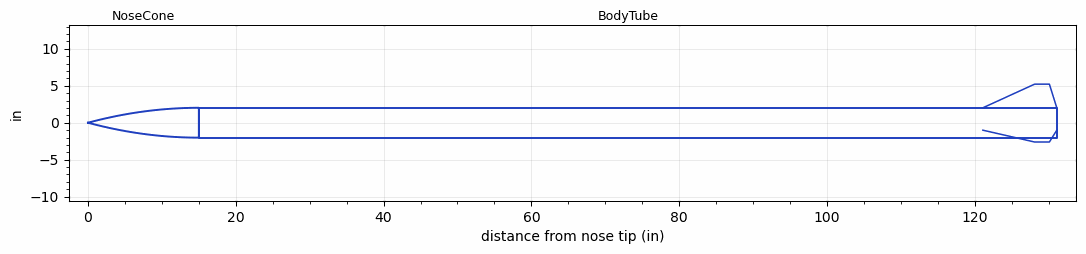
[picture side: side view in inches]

<RASAeroDocument>
 <FileVersion>2</FileVersion>
 <RocketDesign>
  <NoseCone>
   <Length>15</Length>
   <Diameter>4.04</Diameter>
   <Shape>Parabolic</Shape>
   <BluntRadius>0.0625</BluntRadius>
   <Location>0</Location>
  </NoseCone>
  <BodyTube>
   <Length>116.1</Length>
   <Diameter>4.04</Diameter>
   <LaunchShoeArea>0.09</LaunchShoeArea>
   <Location>15</Location>
   <Fin>
    <Count>3</Count>
    <Chord>10</Chord>
    <Span>3.2</Span>
    <SweepDistance>7</SweepDistance>
    <TipChord>2</TipChord>
    <Thickness>0.25</Thickness>
    <LERadius>0.125</LERadius>
    <Location>10</Location>
    <AirfoilSection>Double Wedge</AirfoilSection>
    <FX1>1</FX1>
   </Fin>
  </BodyTube>
  <Surface>Rough Camouflage Paint</Surface>
  <ModifiedBarrowman>True</ModifiedBarrowman>
  <Turbulence>False</Turbulence>
  <UseBooster1>False</UseBooster1>
  <UseBooster2>False</UseBooster2>
 </RocketDesign>
 <LaunchSite>
  <Altitude>4596</Altitude>
  <Pressure>0</Pressure>
  <RodAngle>5</RodAngle>
  <RodLength>18</RodLength>
  <Temperature>100</Temperature>
  <WindSpeed>5</WindSpeed>
 </LaunchSite>
 <Recovery>
  <Altitude1>1000</Altitude1>
  <Altitude2>1500</Altitude2>
  <DeviceType1>Parachute</DeviceType1>
  <DeviceType2>Parachute</DeviceType2>
  <Event1>True</Event1>
  <Event2>True</Event2>
  <Size1>30.57</Size1>
  <Size2>157.2</Size2>
  <EventType1>Apogee</EventType1>
  <EventType2>Altitude</EventType2>
  <CD1>0.75</CD1>
  <CD2>0.928</CD2>
 </Recovery>
 <SimulationList>
  <Simulation>
   <SustainerEngine>N2900-CL  (CTI)</SustainerEngine>
   <SustainerLaunchWt>72.49</SustainerLaunchWt>
   <SustainerNozzleDiameter>2</SustainerNozzleDiameter>
   <SustainerCG>75.91</SustainerCG>
   <SustainerIgnitionDelay>0</SustainerIgnitionDelay>
   <Booster1SeparationDelay>0</Booster1SeparationDelay>
   <Booster1IgnitionDelay>0</Booster1IgnitionDelay>
   <IncludeBooster1>False</IncludeBooster1>
   <Booster2Delay>0</Booster2Delay>
   <IncludeBooster2>False</IncludeBooster2>
   <TimetoApogee>42.08894</TimetoApogee>
   <MaxAltitude>30005.98</MaxAltitude>
   <MaxVelocity>1687.558</MaxVelocity>
  </Simulation>
  <Simulation>
   <SustainerEngine>N2900-CL  (CTI)</SustainerEngine>
   <SustainerLaunchWt>68</SustainerLaunchWt>
   <SustainerNozzleDiameter>2</SustainerNozzleDiameter>
   <SustainerCG>76</SustainerCG>
   <SustainerIgnitionDelay>0</SustainerIgnitionDelay>
   <Booster1SeparationDelay>0</Booster1SeparationDelay>
   <Booster1IgnitionDelay>0</Booster1IgnitionDelay>
   <IncludeBooster1>False</IncludeBooster1>
   <Booster2Delay>0</Booster2Delay>
   <IncludeBooster2>False</IncludeBooster2>
   <TimetoApogee>40.04929</TimetoApogee>
   <MaxAltitude>28667.05</MaxAltitude>
   <MaxVelocity>1763.403</MaxVelocity>
  </Simulation>
  <Simulation>
   <SustainerEngine>N2900-CL  (CTI)</SustainerEngine>
   <SustainerLaunchWt>74.8</SustainerLaunchWt>
   <SustainerNozzleDiameter>2</SustainerNozzleDiameter>
   <SustainerCG>74.5</SustainerCG>
   <SustainerIgnitionDelay>0</SustainerIgnitionDelay>
   <Booster1SeparationDelay>0</Booster1SeparationDelay>
   <Booster1IgnitionDelay>0</Booster1IgnitionDelay>
   <IncludeBooster1>False</IncludeBooster1>
   <Booster2Delay>0</Booster2Delay>
   <IncludeBooster2>False</IncludeBooster2>
   <TimetoApogee>42.83882</TimetoApogee>
   <MaxAltitude>30388.57</MaxAltitude>
   <MaxVelocity>1647.571</MaxVelocity>
  </Simulation>
  <Simulation>
   <SustainerEngine>N2900-CL  (CTI)</SustainerEngine>
   <SustainerLaunchWt>58</SustainerLaunchWt>
   <SustainerNozzleDiameter>2</SustainerNozzleDiameter>
   <SustainerCG>77.77</SustainerCG>
   <SustainerIgnitionDelay>0</SustainerIgnitionDelay>
   <Booster1SeparationDelay>0</Booster1SeparationDelay>
   <Booster1IgnitionDelay>0</Booster1IgnitionDelay>
   <IncludeBooster1>False</IncludeBooster1>
   <Booster2Delay>0</Booster2Delay>
   <IncludeBooster2>False</IncludeBooster2>
   <TimetoApogee>41.11911</TimetoApogee>
   <MaxAltitude>32487.73</MaxAltitude>
   <MaxVelocity>2076.883</MaxVelocity>
  </Simulation>
  <Simulation>
   <SustainerEngine>N2900-CL  (CTI)</SustainerEngine>
   <SustainerLaunchWt>58.7</SustainerLaunchWt>
   <SustainerNozzleDiameter>2</SustainerNozzleDiameter>
   <SustainerCG>77</SustainerCG>
   <SustainerIgnitionDelay>0</SustainerIgnitionDelay>
   <Booster1SeparationDelay>0</Booster1SeparationDelay>
   <Booster1IgnitionDelay>0</Booster1IgnitionDelay>
   <IncludeBooster1>False</IncludeBooster1>
   <Booster2Delay>0</Booster2Delay>
   <IncludeBooster2>False</IncludeBooster2>
   <TimetoApogee>46.67817</TimetoApogee>
   <MaxAltitude>39360.13</MaxAltitude>
   <MaxVelocity>2145.872</MaxVelocity>
  </Simulation>
  <Simulation>
   <SustainerEngine>N2900-CL  (CTI)</SustainerEngine>
   <SustainerLaunchWt>61</SustainerLaunchWt>
   <SustainerNozzleDiameter>2</SustainerNozzleDiameter>
   <SustainerCG>77.2</SustainerCG>
   <SustainerIgnitionDelay>0</SustainerIgnitionDelay>
   <Booster1SeparationDelay>0</Booster1SeparationDelay>
   <Booster1IgnitionDelay>0</Booster1IgnitionDelay>
   <IncludeBooster1>False</IncludeBooster1>
   <Booster2Delay>0</Booster2Delay>
   <IncludeBooster2>False</IncludeBooster2>
   <TimetoApogee>46.5182</TimetoApogee>
   <MaxAltitude>38396.11</MaxAltitude>
   <MaxVelocity>2063.828</MaxVelocity>
  </Simulation>
 </SimulationList>
</RASAeroDocument>
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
